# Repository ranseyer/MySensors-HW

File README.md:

View this project on [CADLAB.io](https://cadlab.io/project/1149). 

# MySensors-HW

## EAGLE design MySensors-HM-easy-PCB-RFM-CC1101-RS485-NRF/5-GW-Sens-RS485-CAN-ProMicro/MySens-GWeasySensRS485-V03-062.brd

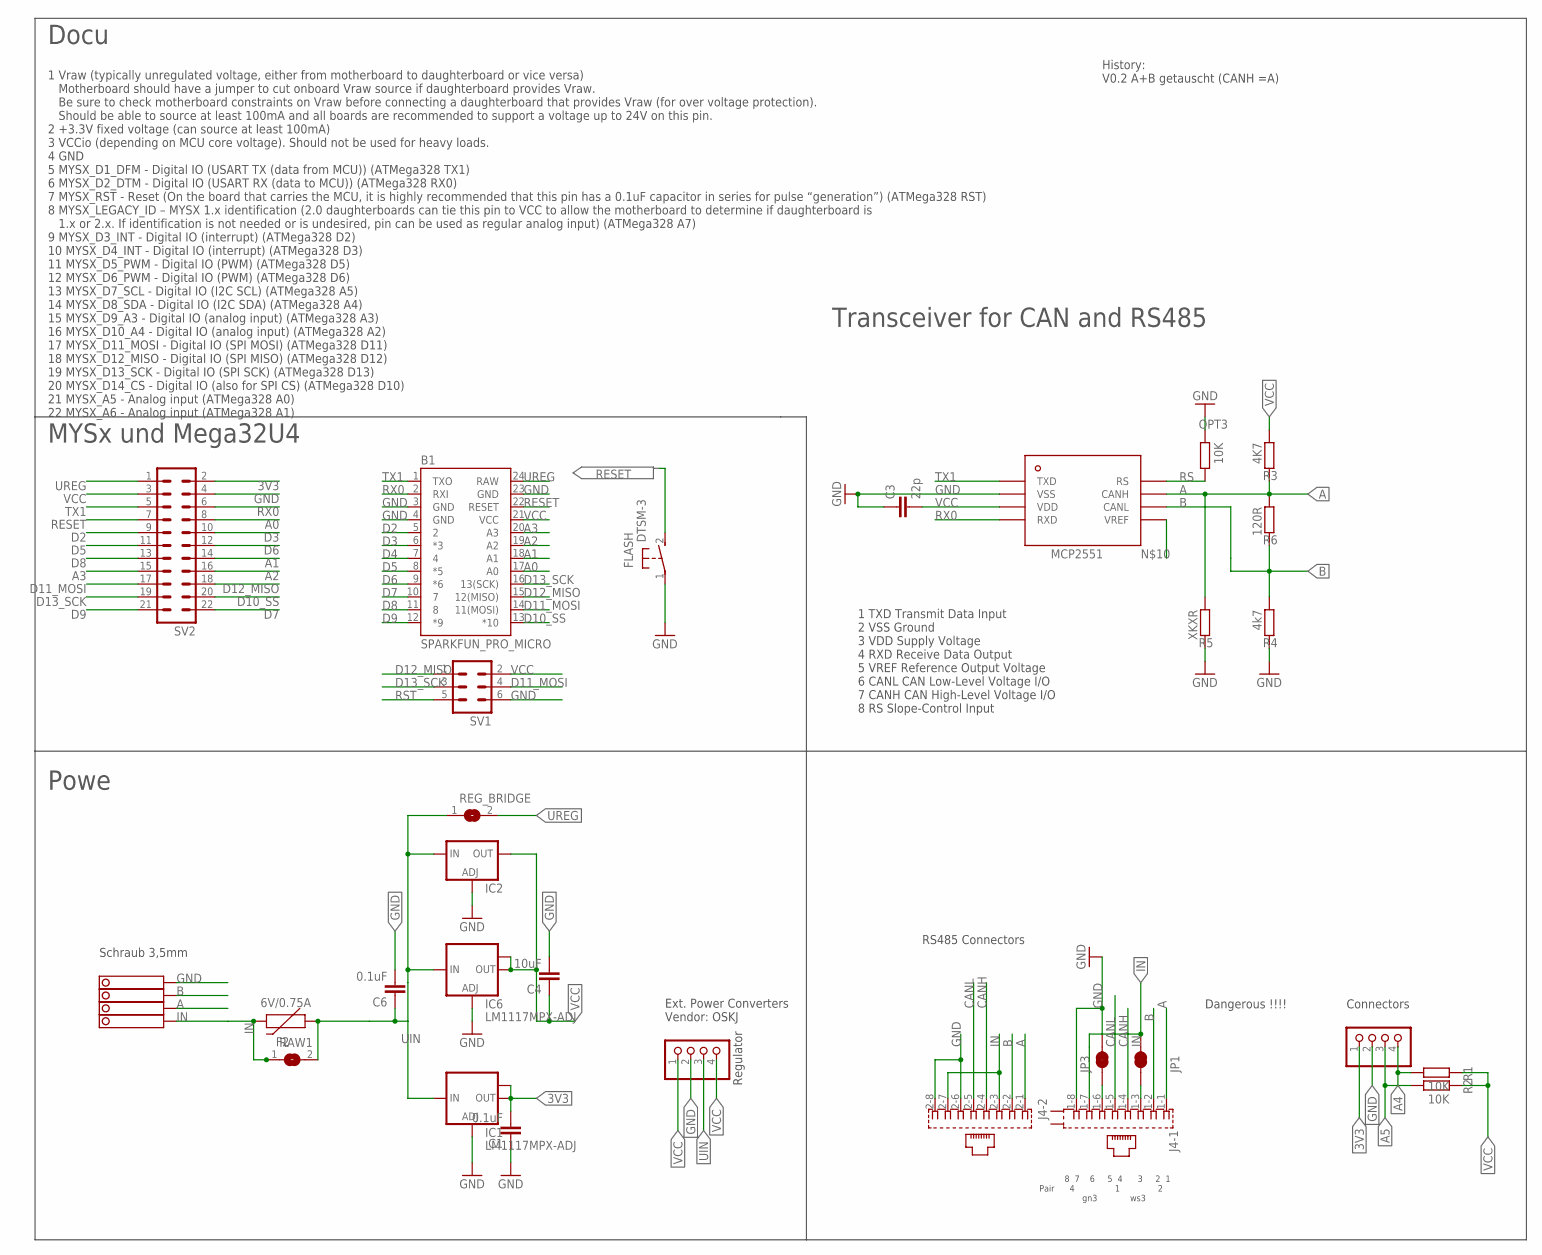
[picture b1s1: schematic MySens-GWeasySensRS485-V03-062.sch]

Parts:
B1: SPARKFUN_PRO_MICRO
C1, C6: 0.1uF; C1206
C3: 22p; C0805
C4: 10uF; C1210
F2: 6V/0.75A; 1206
FLASH: DTSM-3
I2C: PINHD-1X04_2.54-S; 1X04-S
IC1, IC6: LM1117MPX-ADJ; SOT223
IC2: LD117ADT50TR; DPACK
J4: RJ45_2X_S
JP1, JP3: JUMPER-SMT_2_NC_TRACE_SILK; SMT-JUMPER_2_NC_TRACE_SILK
OPT3: 10K; R0805
R1, R2: 10K; R0805
R3: 4K7; R0805
R4: 4k7; R0805
R5: XKXR; R0805
R6: 120R; R0805
RAW1: SJ
REG_BRIDGE: SJ
STEPDWN: PINHD-1X04_2.54-S; 1X04-S
SV1: MA03-2
SV2: MA11-2
U$1: MCP2551; SOIC-8
X4: 1751264

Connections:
1: J4.1-3 (3), JP1.1
2: J4.1-6 (6), JP3.1
3V3: C1.2, I2C.1, IC1.2 (OUT), IC1.TAB (OUT1), SV2.2
A: J4.1-1 (1), J4.2-1 (1), R3.2, R5.1, R6.1, U$1.CANH, X4.2
A0: B1.17 (A0), SV2.8
A1: B1.18 (A1), SV2.14
A2: B1.19 (A2), SV2.16
A3: B1.20 (A3), SV2.15
A4: I2C.4, R1.2
A5: I2C.3, R2.2
B: J4.1-2 (2), J4.2-2 (2), R4.1, R6.2, U$1.CANL, X4.3
CANH: J4.1-4 (4), J4.2-4 (4)
CANL: J4.1-5 (5), J4.2-5 (5)
D2: B1.5 (2), SV2.9
D3: B1.6 (*3), SV2.10
D4: B1.7 (4)
D5: B1.8 (*5), SV2.11
D6: B1.9 (*6), SV2.12
D7: B1.10 (7), SV2.22
D8: B1.11 (8), SV2.13
D9: B1.12 (*9), SV2.21
D10_SS: B1.13 (*10), SV2.20
D11_MOSI: B1.14 (11(MOSI)), SV1.4, SV2.17
D12_MISO: B1.15 (12(MISO)), SV1.1, SV2.18
D13_SCK: B1.16 (13(SCK)), SV1.3, SV2.19
GND: B1.3 (GND), B1.4 (GND), B1.23 (GND), C1.1, C3.1, C4.2, C6.2, FLASH.1, I2C.2, IC1.1 (ADJ), IC2.1 (ADJ), IC6.1 (ADJ), J4.1-8 (8), J4.2-6 (6), J4.2-8 (8), JP3.2, OPT3.1, R4.2, R5.2, STEPDWN.2, SV1.6, SV2.4, U$1.VSS, X4.4
IN: F2.2, J4.1-7 (7), J4.2-3 (3), J4.2-7 (7), JP1.2, RAW1.1, X4.1
RESET: B1.22 (RESET), FLASH.2, SV2.7
RS: OPT3.2, U$1.RS
RST: SV1.5
RX0: B1.2 (RXI), SV2.6, U$1.RXD
TX1: B1.1 (TXO), SV2.5, U$1.TXD
UIN: C6.1, F2.1, IC1.3 (IN), IC2.3 (IN), IC6.3 (IN), RAW1.2, REG_BRIDGE.1, STEPDWN.3
UREG: B1.24 (RAW), REG_BRIDGE.2, SV2.1
VCC: B1.21 (VCC), C3.2, C4.1, IC2.4 (OUT), IC6.2 (OUT), IC6.TAB (OUT1), R1.1, R2.1, R3.1, STEPDWN.1, STEPDWN.4, SV1.2, SV2.3, U$1.VDD

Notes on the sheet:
Connectors
8 7 6 5 4 3 2 1 Pair 4 1 2 gn3 ws3
Dangerous !!!!
RS485 Connectors
Schraub 3,5mm
Ext. Power Converters Vendor: OSKJ
Regulator
1 TXD Transmit Data Input 2 VSS Ground 3 VDD Supply Voltage 4 RXD Receive Data Output 5 VREF Reference Output Voltage 6 CANL CAN Low-Level Voltage I/O 7 CANH CAN High-Level Voltage I/O 8 RS Slope-Control Input
1 Vraw (typically unregulated voltage, either from motherboard to daughterboard or vice versa) Motherboard should have a jumper to cut onboard Vraw source if daughterboard provides Vraw. Be sure to check motherboard constraints on Vraw before connecting a daughterboard that provides Vraw (for over 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
Transceiver for CAN and RS485
MYSx und Mega32U4
Powe
Docu
History: V0.2 A+B getauscht (CANH =A)

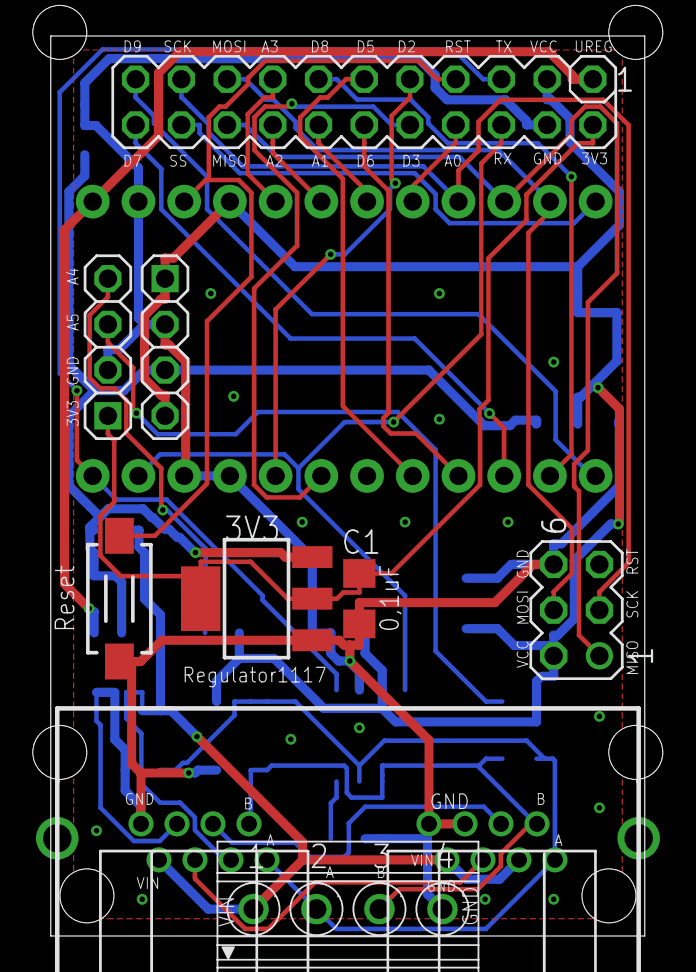
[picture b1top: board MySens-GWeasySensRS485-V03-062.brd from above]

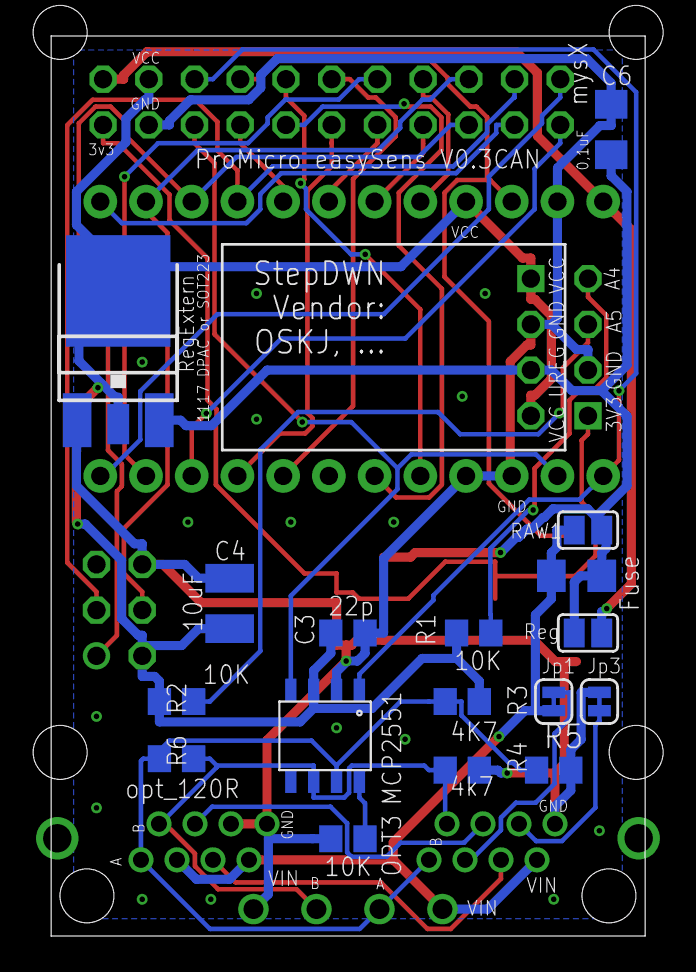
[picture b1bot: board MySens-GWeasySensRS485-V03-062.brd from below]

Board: 2 copper layers, 33.0 x 50.0 mm, 28 parts (18 on the bottom side), 33 nets.

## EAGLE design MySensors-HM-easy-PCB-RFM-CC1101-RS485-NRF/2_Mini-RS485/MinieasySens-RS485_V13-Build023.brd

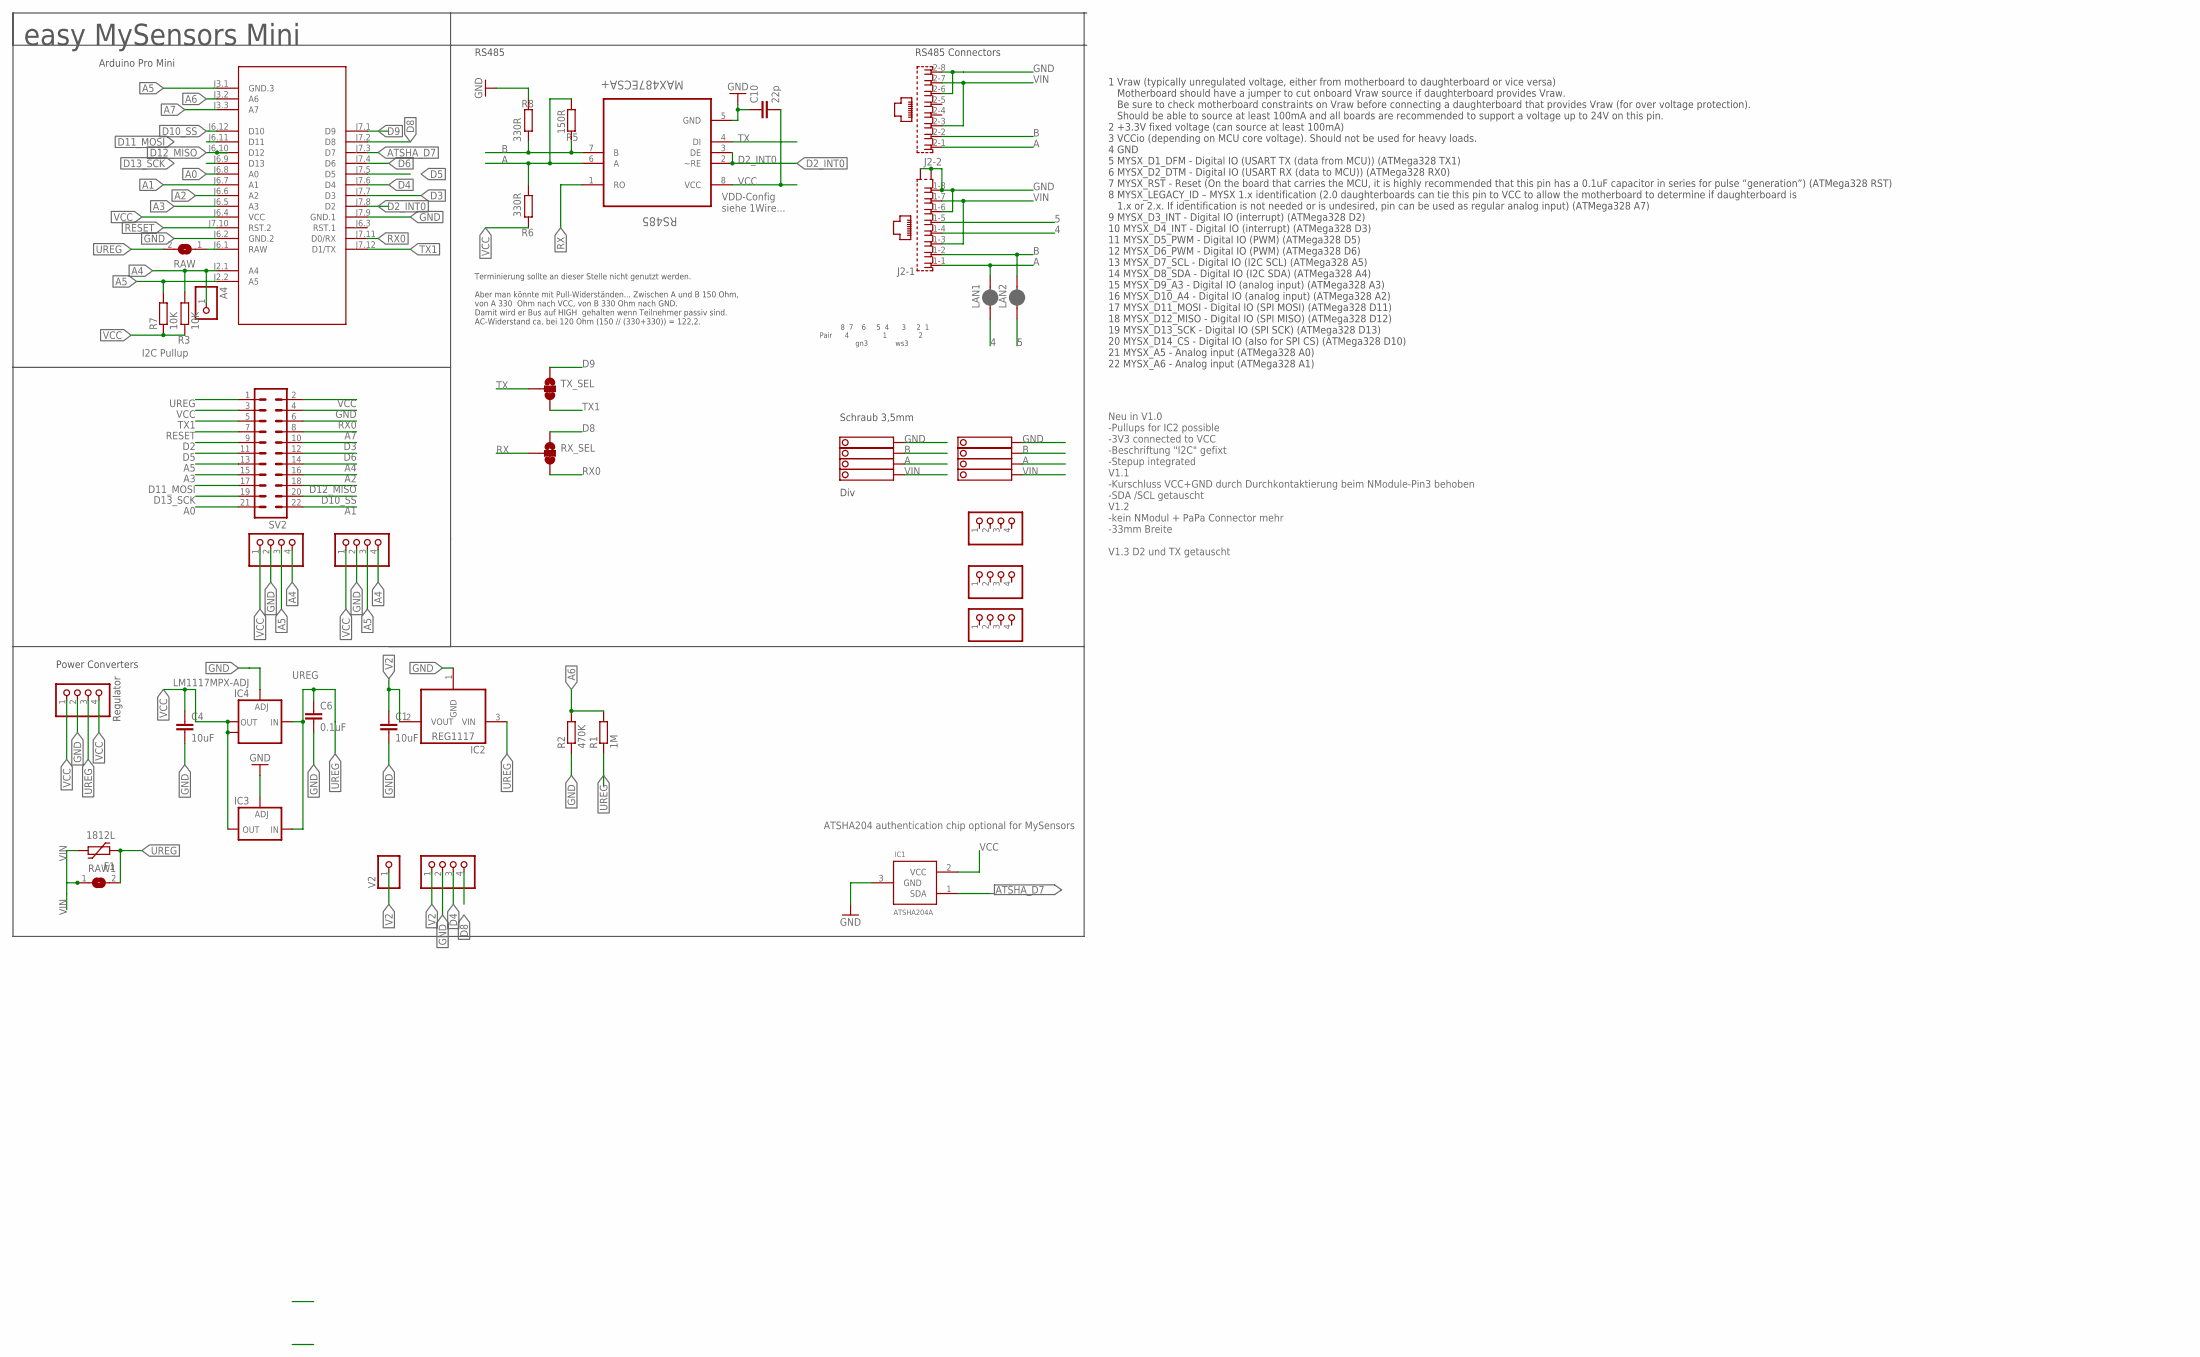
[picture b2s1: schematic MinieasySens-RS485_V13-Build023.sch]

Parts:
A4: PINHD-1X1; 1X01
BH1750: PINHD-1X04_2.54-S; 1X04-S
C1, C4: 10uF; C1210
C6: 0.1uF; C1206
C10: 22p; C0805
F1: 1812L
I2C-1: PINHD-1X04_2.54-S; 1X04-S
IC1: ATSHA204A; SOT23
IC2: REG1117; SOT223
IC3: LD117ADT50TR; DPACK
IC4: LM1117MPX-ADJ; SOT223
J2: RJ45_2X_NARROW_SHILDPINS_NOCASE
JP1, JP2, JP4: PINHD-1X04_2.54-S; 1X04-S
LAN1, LAN2: JUMPER-SMT_2_NC_PASTE_SILK; SMT-JUMPER_2_NC_PASTE_SILK
M1: ARDUINO-PRO-MINI-3.3V#NP; ARDUINO-PRO-MINI#NP
R1: 1M; R0805
R2: 470K; R0805
R3, R7: 10K; R0805
R5: 150R; R0805
R6, R8: 330R; R0805
RAW, RAW1: SJ
RS485: MAX487ECSA+; SOIC127P600X175-8N
RX_SEL: JUMPER-SMT_3_1-NC_TRACE_SILK; SMT-JUMPER_3_1-NC_TRACE_SILK
STEPDWN: PINHD-1X04_2.54-S; 1X04-S
SV2: MA11-2
TX_SEL: JUMPER-SMT_3_1-NC_TRACE_SILK; SMT-JUMPER_3_1-NC_TRACE_SILK
V2: PINHD-1X1; 1X01
V2-: PINHD-1X04_2.54-S; 1X04-S
X1, X4: 1751264

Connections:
4: J2.1-4 (4), LAN1.1
5: J2.1-5 (5), LAN2.1
A: J2.1-1 (1), J2.2-1 (1), LAN1.2, R5.1, R6.2, RS485.6 (A), X1.2, X4.2
A0: M1.J6.8 (A0), SV2.21
A1: M1.J6.7 (A1), SV2.22
A2: M1.J6.6 (A2), SV2.16
A3: M1.J6.5 (A3), SV2.15
A4: A4.1, BH1750.4, I2C-1.4, M1.J2.1 (A4), R3.2, SV2.14
A5: BH1750.3, I2C-1.3, M1.J2.2 (A5), M1.J3.1 (GND.3), R7.2, SV2.13
A6: M1.J3.2 (A6), R1.2, R2.2
A7: M1.J3.3 (A7), SV2.8
ATSHA_D7: IC1.1 (SDA), M1.J7.3 (D7)
B: J2.1-2 (2), J2.2-2 (2), LAN2.2, R5.2, R8.1, RS485.7 (B), X1.3, X4.3
D2: SV2.9
D2_INT0: M1.J7.8 (D2), RS485.2 (~RE), RS485.3 (DE)
D3: M1.J7.7 (D3), SV2.10
D4: M1.J7.6 (D4), V2-.3
D5: M1.J7.5 (D5), SV2.11
D6: M1.J7.4 (D6), SV2.12
D8: M1.J7.2 (D8), RX_SEL.1, V2-.4
D9: M1.J7.1 (D9), TX_SEL.1
D10_SS: M1.J6.12 (D10), SV2.20
D11_MOSI: M1.J6.11 (D11), SV2.17
D12_MISO: M1.J6.10 (D12), SV2.18
D13_SCK: M1.J6.9 (D13), SV2.19
GND: BH1750.2, C1.2, C4.2, C6.2, C10.1, I2C-1.2, IC1.3 (GND), IC2.1 (GND), IC3.1 (ADJ), IC4.1 (ADJ), J2.1-6 (6), J2.1-8 (8), J2.2-6 (6), J2.2-8 (8), J2.G1 (S1), J2.G3 (S2), M1.J6.2 (GND.2), M1.J7.9 (GND.1), R2.1, R8.2, RS485.5 (GND), STEPDWN.2, SV2.4, V2-.2, X1.4, X4.4
RAW: M1.J6.1 (RAW), RAW.1
RESET: M1.J7.10 (RST.2), SV2.7
RX: RS485.1 (RO), RX_SEL.2
RX0: M1.J7.11 (D0/RX), RX_SEL.3, SV2.6
TX: RS485.4 (DI), TX_SEL.2
TX1: M1.J7.12 (D1/TX), SV2.5, TX_SEL.3
UREG: C6.1, F1.P$1 (1), IC2.3 (VIN), IC3.3 (IN), IC4.3 (IN), R1.1, RAW.2, RAW1.2, STEPDWN.3, SV2.1
V2: C1.1, IC2.2 (VOUT), V2.1, V2-.1
VCC: BH1750.1, C4.1, C10.2, I2C-1.1, IC1.2 (VCC), IC3.4 (OUT), IC4.2 (OUT), IC4.TAB (OUT1), M1.J6.4 (VCC), R3.1, R6.1, R7.1, RS485.8 (VCC), STEPDWN.1, STEPDWN.4, SV2.2, SV2.3
VIN: F1.P$2 (2), J2.1-3 (3), J2.1-7 (7), J2.2-3 (3), J2.2-7 (7), RAW1.1, X1.1, X4.1

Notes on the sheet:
easy MySensors Mini
Arduino Pro Mini
ATSHA204 authentication chip optional for MySensors
Div
Neu in V1.0 -Pullups for IC2 possible -3V3 connected to VCC -Beschriftung "I2C" gefixt -Stepup integrated V1.1 -Kurschluss VCC+GND durch Durchkontaktierung beim NModule-Pin3 behoben -SDA /SCL getauscht V1.2 -kein NModul + PaPa Connector mehr -33mm Breite V1.3 D2 und TX getauscht
I2C Pullup
Power Converters
RS485
VDD-Config siehe 1Wire...
Terminierung sollte an dieser Stelle nicht genutzt werden. Aber man könnte mit Pull-Widerständen... Zwischen A und B 150 Ohm, von A 330 Ohm nach VCC, von B 330 Ohm nach GND. Damit wird er Bus auf HIGH gehalten wenn Teilnehmer passiv sind. AC-Widerstand ca. bei 120 Ohm (150 // (330+330)) = 122,2.
Schraub 3,5mm
8 7 6 5 4 3 2 1 Pair 4 1 2 gn3 ws3
Regulator
RS485 Connectors
1 Vraw (typically unregulated voltage, either from motherboard to daughterboard or vice versa) Motherboard should have a jumper to cut onboard Vraw source if daughterboard provides Vraw. Be sure to check motherboard constraints on Vraw before connecting a daughterboard that provides Vraw (for over 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

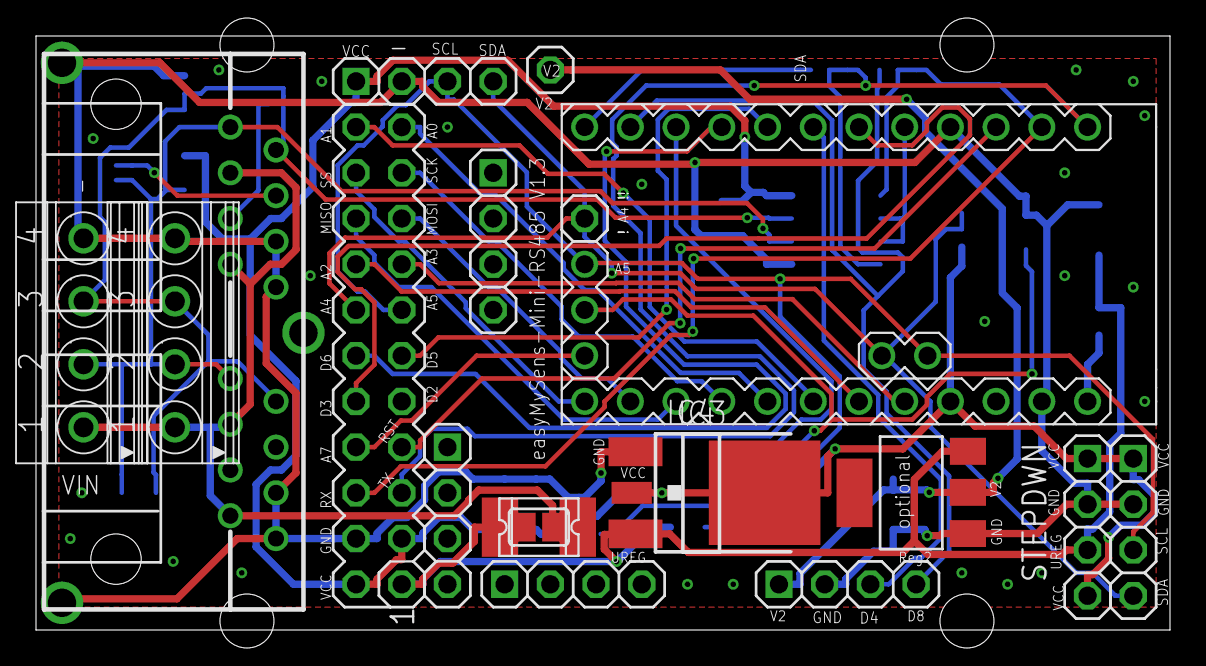
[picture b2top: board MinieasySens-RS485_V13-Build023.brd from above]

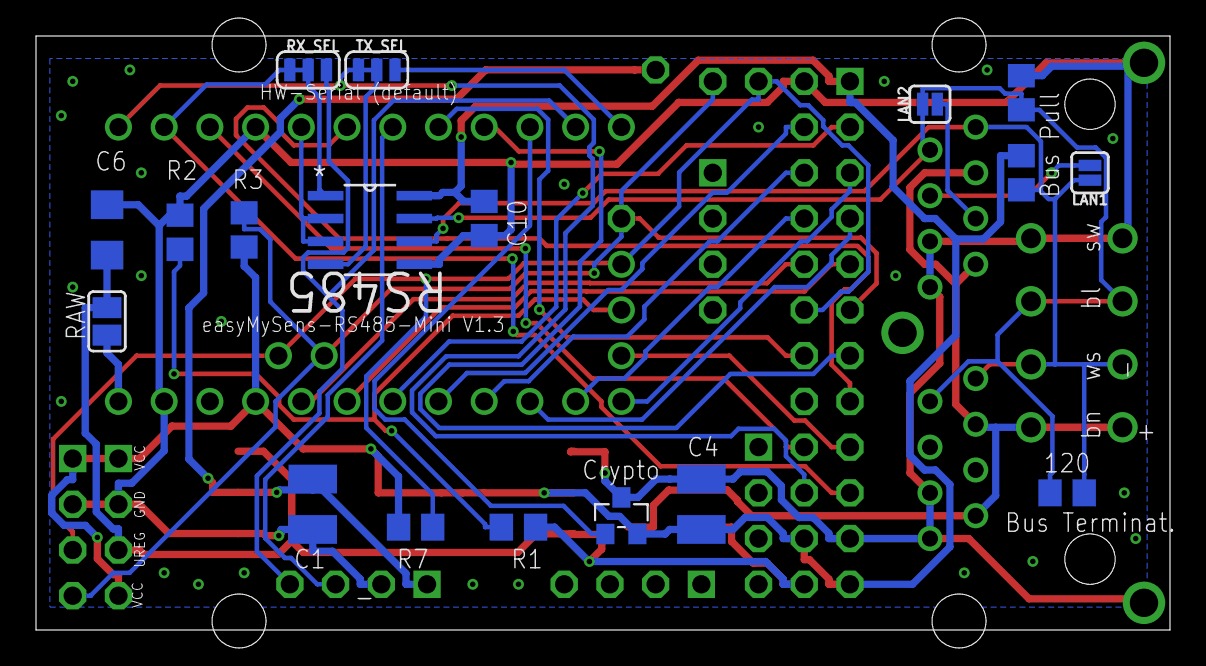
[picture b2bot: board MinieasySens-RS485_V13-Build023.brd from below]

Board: 2 copper layers, 63.0 x 33.0 mm, 37 parts (18 on the bottom side), 35 nets.

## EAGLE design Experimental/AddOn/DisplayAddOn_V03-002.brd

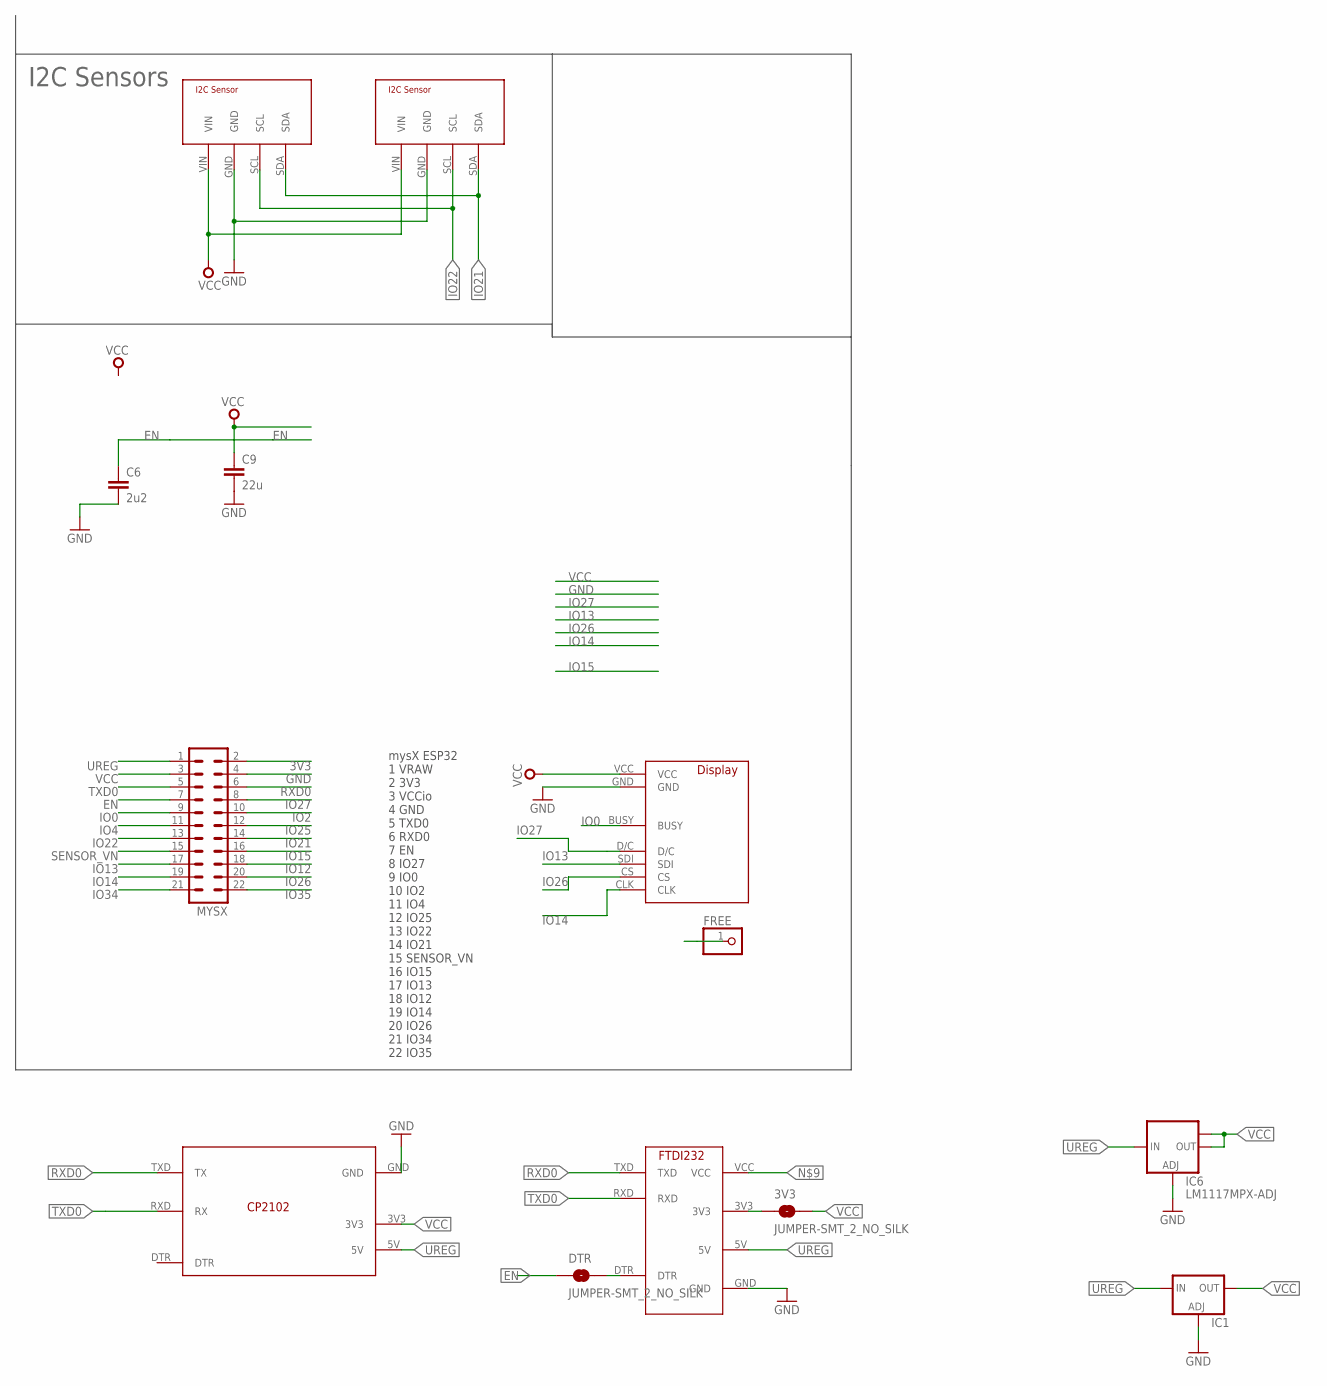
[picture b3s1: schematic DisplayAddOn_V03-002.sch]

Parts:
3V3: JUMPER-SMT_2_NO_SILK; SMT-JUMPER_2_NO_SILK
C6: 2u2; C0805
C9: 22u; C0805
DTR: JUMPER-SMT_2_NO_SILK; SMT-JUMPER_2_NO_SILK
FREE: PINHD-1X1; 1X01
HELTEK: ZUCZUG_1.54; ZUCZUG_1.54INCH
IC1: LD117ADT50TR; DPACK
IC6: LM1117MPX-ADJ; SOT223
MYSX: MA11-2
U$1: CP2101; CP2101-BEAKOUT
U$2, U$4: I2C-BREAKOUT; I2C_BREAKOUT
U$3: FTDI232; FTDI232-LARGE-LESS-PINS

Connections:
3V3: MYSX.2
EN: C6.1, DTR.1, MYSX.7
FREE: FREE.1
GND: C6.2, C9.2, HELTEK.GND, IC1.1 (ADJ), IC6.1 (ADJ), MYSX.4, U$1.GND, U$2.GND, U$3.GND, U$4.GND
IO0: HELTEK.BUSY, MYSX.9
IO2: MYSX.10
IO4: MYSX.11
IO12: MYSX.18
IO13: HELTEK.SDI, MYSX.17
IO14: HELTEK.CLK, MYSX.19
IO15: MYSX.16
IO21: MYSX.14, U$2.SDA, U$4.SDA
IO22: MYSX.13, U$2.SCL, U$4.SCL
IO25: MYSX.12
IO26: HELTEK.CS, MYSX.20
IO27: HELTEK.D/C, MYSX.8
IO34: MYSX.21
IO35: MYSX.22
unnamed: DTR.2, U$3.DTR
unnamed: 3V3.1, U$3.3V3
RXD0: MYSX.6, U$1.TXD (TX), U$3.TXD
SENSOR_VN: MYSX.15
TXD0: MYSX.5, U$1.RXD (RX), U$3.RXD
UREG: IC1.3 (IN), IC6.3 (IN), MYSX.1, U$1.5V, U$3.5V
VCC: 3V3.2, C9.1, HELTEK.VCC, IC1.4 (OUT), IC6.2 (OUT), IC6.TAB (OUT1), MYSX.3, U$1.3V3, U$2.VIN, U$4.VIN

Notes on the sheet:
mysX ESP32 1 VRAW 2 3V3 3 VCCio 4 GND 5 TXD0 6 RXD0 7 EN 8 IO27 9 IO0 10 IO2 11 IO4 12 IO25 13 IO22 14 IO21 15 SENSOR_VN 16 IO15 17 IO13 18 IO12 19 IO14 20 IO26 21 IO34 22 IO35
I2C Sensors

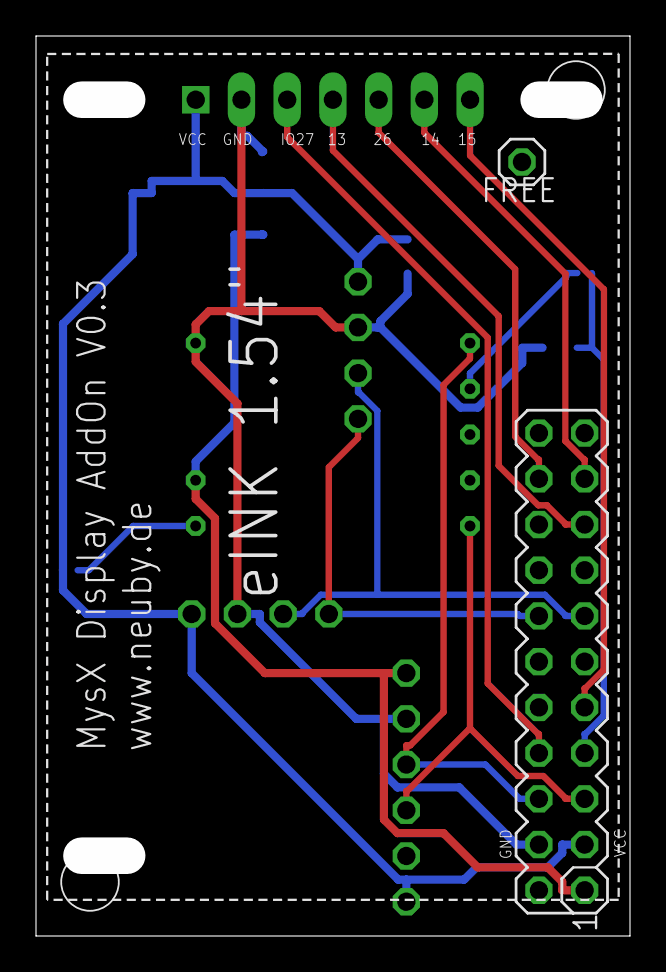
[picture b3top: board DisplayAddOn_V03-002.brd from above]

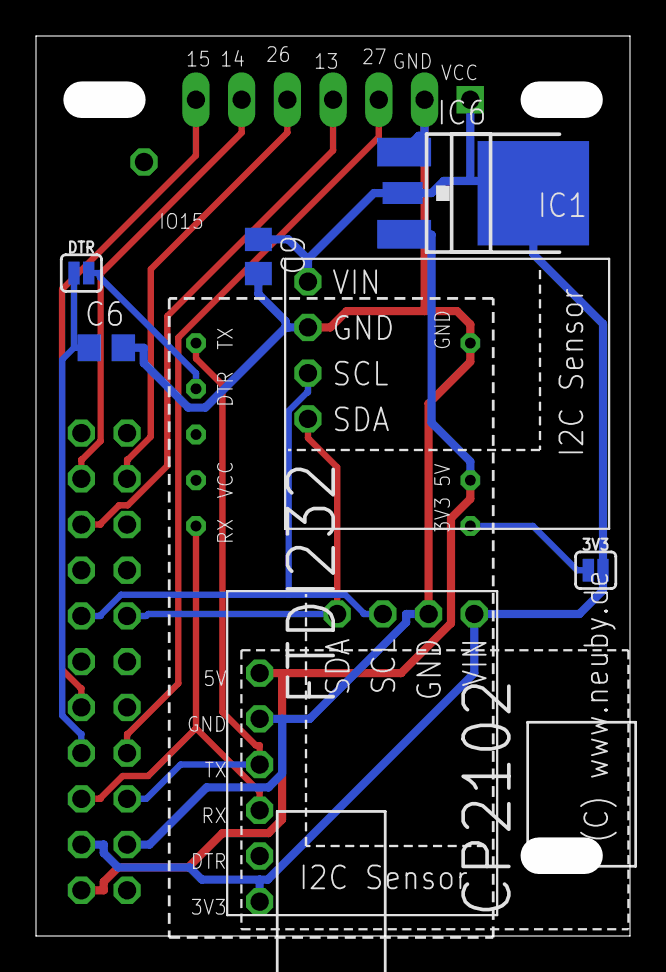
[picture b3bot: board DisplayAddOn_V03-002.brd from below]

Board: 2 copper layers, 31.0 x 48.0 mm, 13 parts (10 on the bottom side), 15 nets.

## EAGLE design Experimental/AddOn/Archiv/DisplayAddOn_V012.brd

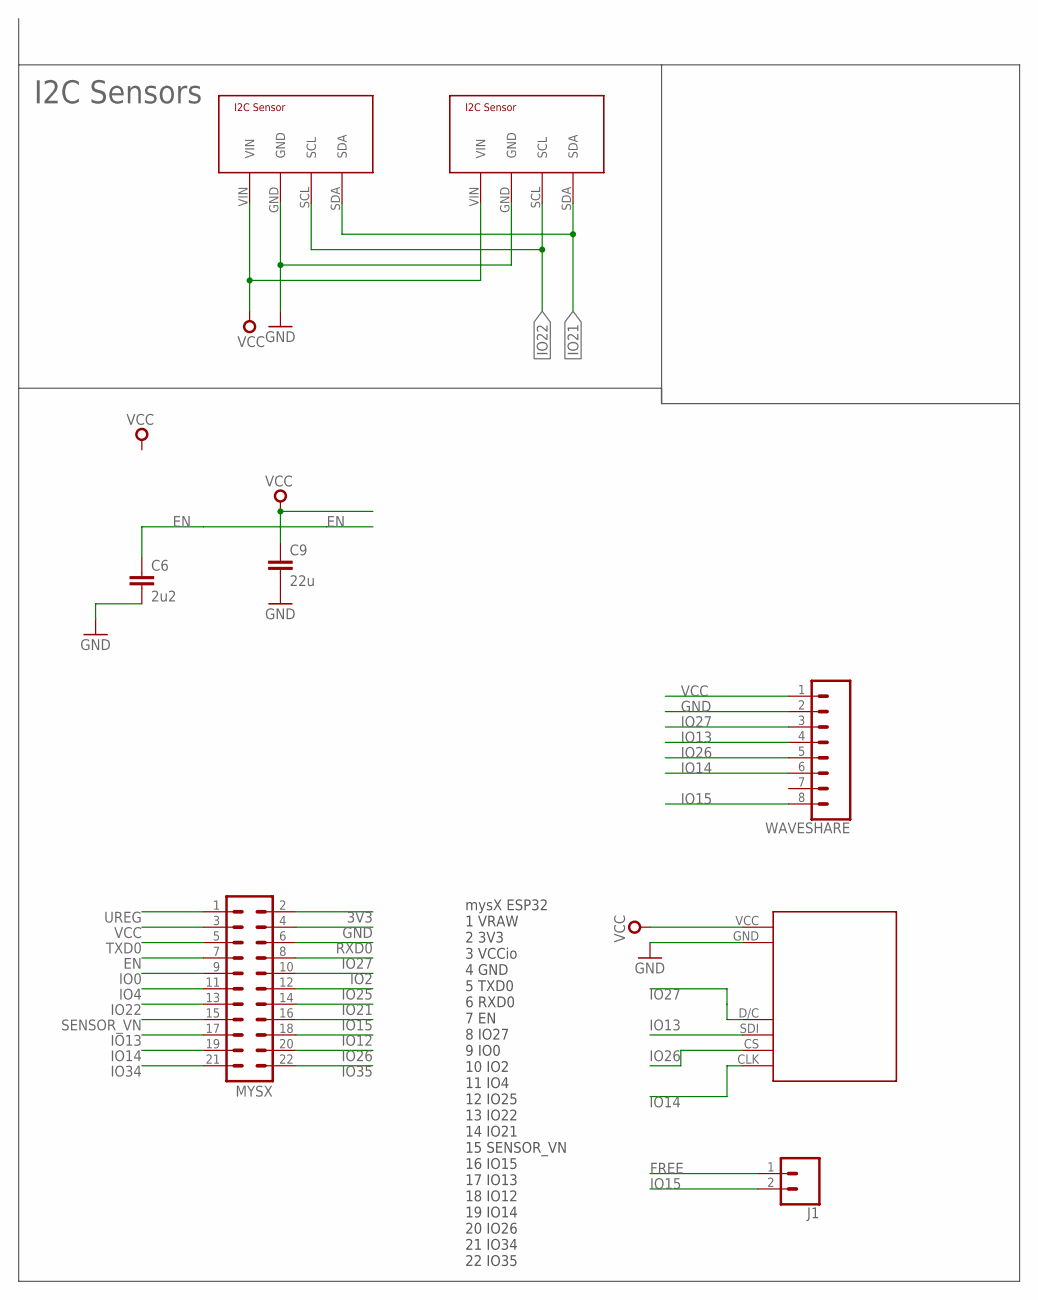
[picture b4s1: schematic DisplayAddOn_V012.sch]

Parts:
C6: 2u2; C0805
C9: 22u; C0805
HELTEK: HELTEC_1.54STANDARD1; HELTEC_1.54INCH
J1: CONN_02; 1X02
MYSX: MA11-2
U$2, U$4: I2C-BREAKOUT; I2C_BREAKOUT
WAVESHARE: CONN_08"; 1X08

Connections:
3V3: MYSX.2
EN: C6.1, MYSX.7
FREE: J1.1
GND: C6.2, C9.2, HELTEK.GND, MYSX.4, U$2.GND, U$4.GND, WAVESHARE.2
IO0: MYSX.9
IO2: MYSX.10
IO4: MYSX.11
IO12: MYSX.18
IO13: HELTEK.SDI, MYSX.17, WAVESHARE.4
IO14: HELTEK.CLK, MYSX.19, WAVESHARE.6
IO15: J1.2, MYSX.16, WAVESHARE.8
IO21: MYSX.14, U$2.SDA, U$4.SDA
IO22: MYSX.13, U$2.SCL, U$4.SCL
IO25: MYSX.12
IO26: HELTEK.CS, MYSX.20, WAVESHARE.5
IO27: HELTEK.D/C, MYSX.8, WAVESHARE.3
IO34: MYSX.21
IO35: MYSX.22
RXD0: MYSX.6
SENSOR_VN: MYSX.15
TXD0: MYSX.5
UREG: MYSX.1
VCC: C9.1, HELTEK.VCC, MYSX.3, U$2.VIN, U$4.VIN, WAVESHARE.1

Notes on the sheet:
mysX ESP32 1 VRAW 2 3V3 3 VCCio 4 GND 5 TXD0 6 RXD0 7 EN 8 IO27 9 IO0 10 IO2 11 IO4 12 IO25 13 IO22 14 IO21 15 SENSOR_VN 16 IO15 17 IO13 18 IO12 19 IO14 20 IO26 21 IO34 22 IO35
I2C Sensors

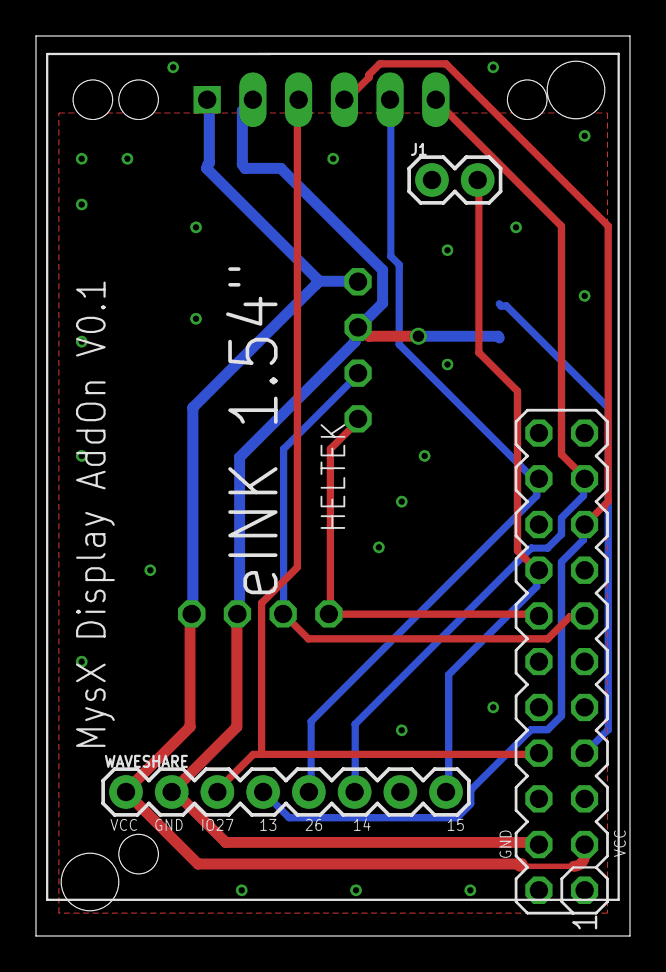
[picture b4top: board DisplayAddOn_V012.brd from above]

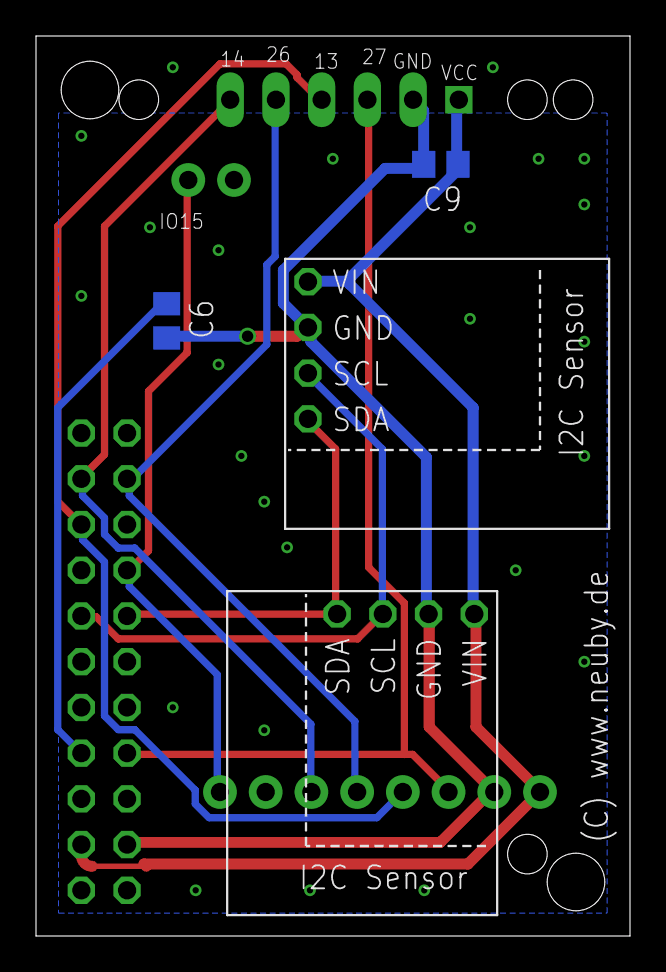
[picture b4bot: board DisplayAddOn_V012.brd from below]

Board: 2 copper layers, 33.0 x 50.0 mm, 8 parts (4 on the bottom side), 10 nets.

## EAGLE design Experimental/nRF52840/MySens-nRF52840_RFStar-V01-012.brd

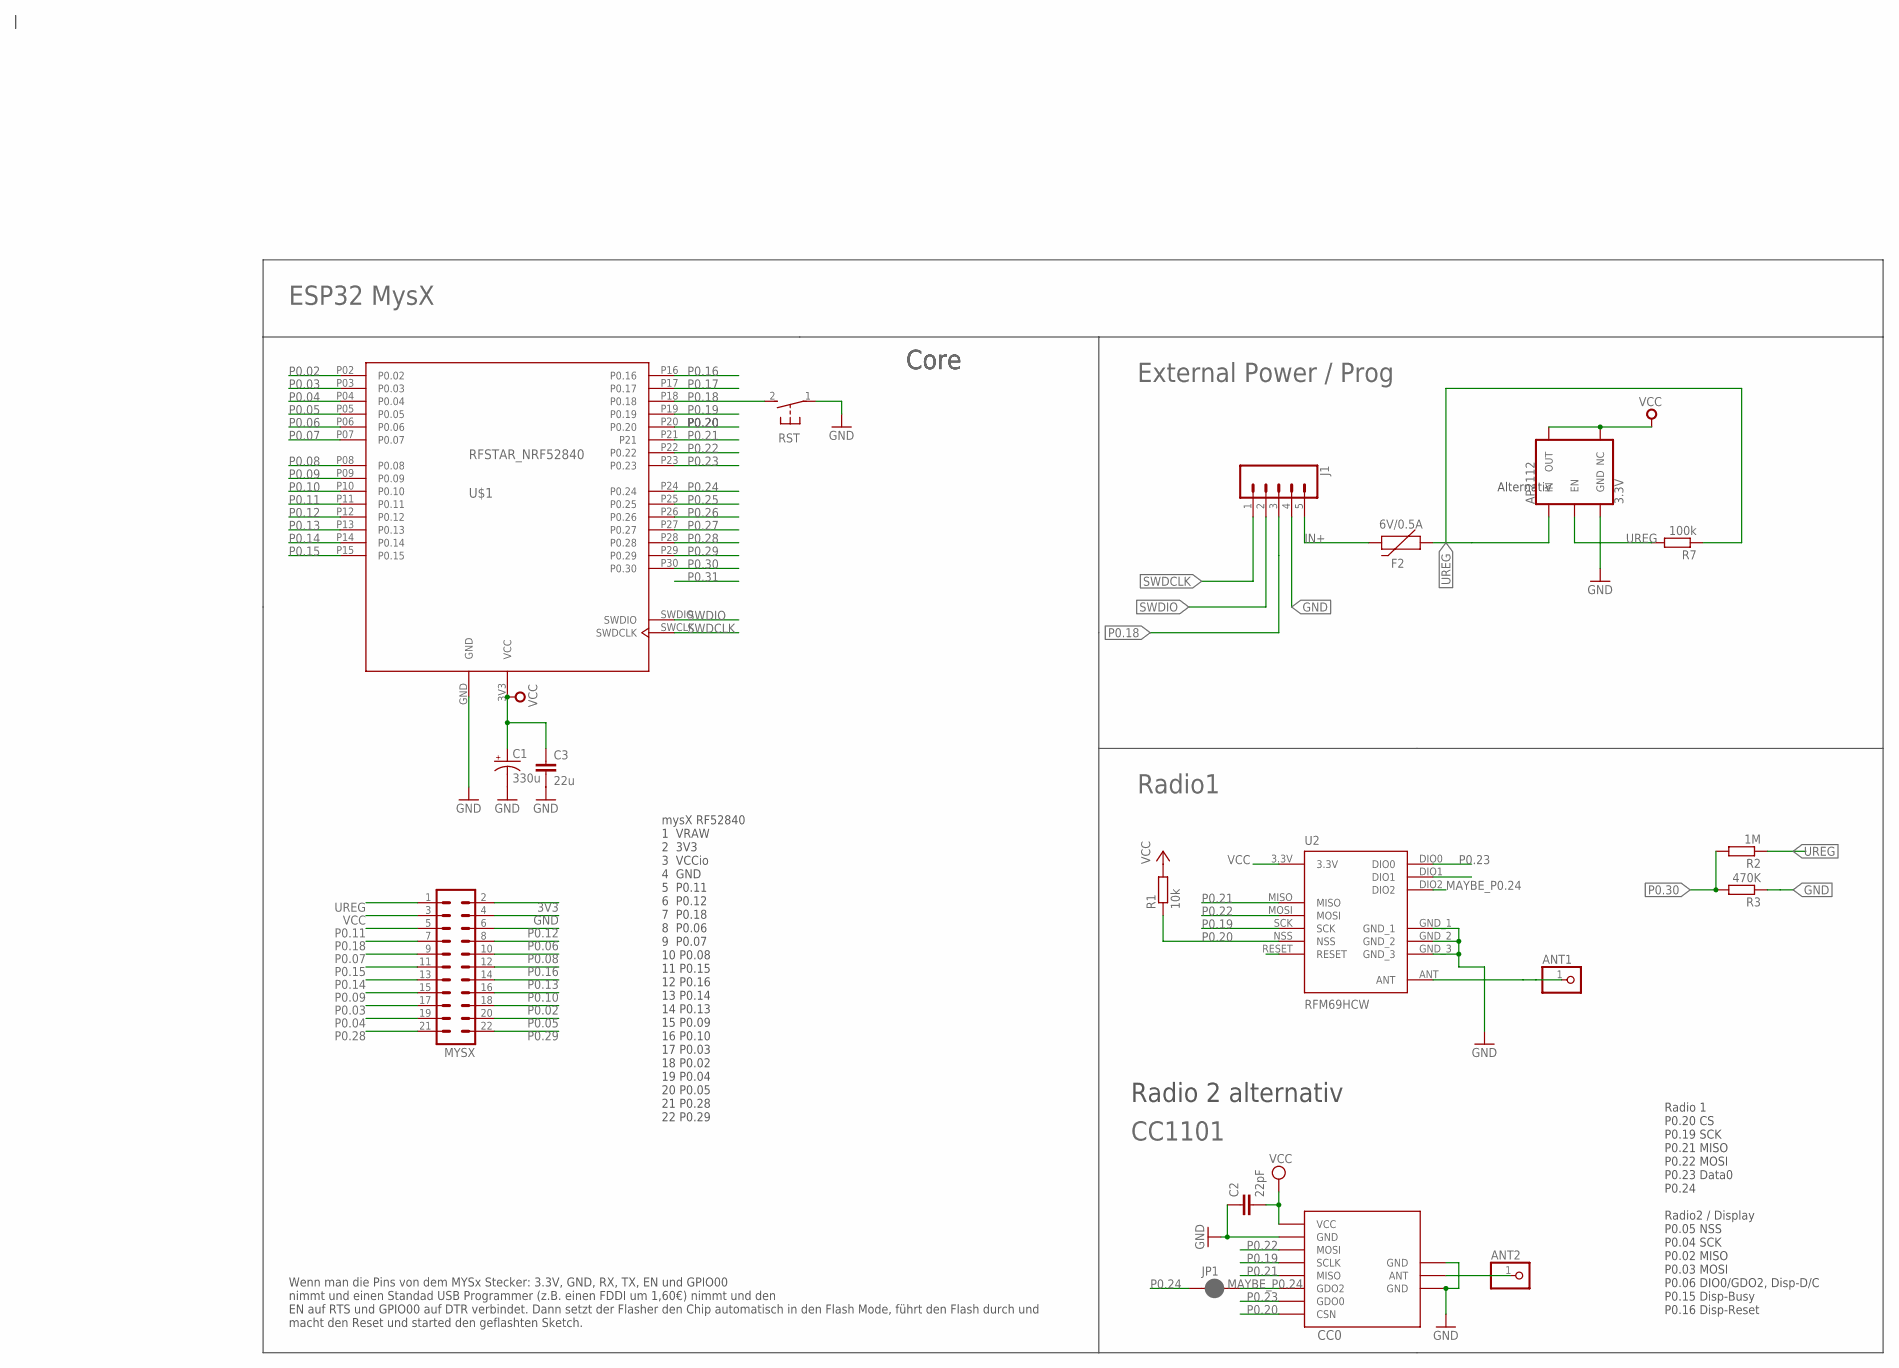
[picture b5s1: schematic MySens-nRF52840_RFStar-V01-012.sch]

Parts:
ANT1, ANT2: PINHD-1X1; 1X01
AP2112: 3.3V; SOT23-5
C1: 330u; VISHAY_C
C2: 22pF; C0805
C3: 22u; C0805
CC0: CC1101; CC1101_MODULE1_SMD
F2: 6V/0.5A; 1206
J1: CONN_05LOCK; 1X05_LOCK
JP1: JUMPER-SMT_2_NC_PASTE_NO-SILK; SMT-JUMPER_2_NC_PASTE_NO-SILK
MYSX: MA11-2
R1: 10k; M0805
R2: 1M; M0805
R3: 470K; M0805
R7: 100k; M0805
RST: DTSM-3
U2: RFM69HCW; RFM69HCW-XXXS2
U$1: RFSTAR_NRF52840

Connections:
3V3: MYSX.2
ANT0: ANT2.1, CC0.ANT
ANT1: ANT1.1, U2.ANT
GND: AP2112.2 (GND), C1.-, C2.1, C3.2, CC0.GND@0 (GND), CC0.GND@1 (GND), CC0.GND@2 (GND), J1.4, MYSX.4, R3.1, RST.1, U2.GND_1, U2.GND_2, U2.GND_3, U$1.GND
IN+: F2.2, J1.5
MAYBE_P0.24: CC0.GDO2, JP1.2, U2.DIO2
unnamed: AP2112.3 (EN), R7.2
P0.02: MYSX.18, U$1.P02 (P0.02)
P0.03: MYSX.17, U$1.P03 (P0.03)
P0.04: MYSX.19, U$1.P04 (P0.04)
P0.05: MYSX.20, U$1.P05 (P0.05)
P0.06: MYSX.8, U$1.P06 (P0.06)
P0.07: MYSX.9, U$1.P07 (P0.07)
P0.08: MYSX.10, U$1.P08 (P0.08)
P0.09: MYSX.15, U$1.P09 (P0.09)
P0.10: MYSX.16, U$1.P10 (P0.10)
P0.11: MYSX.5, U$1.P11 (P0.11)
P0.12: MYSX.6, U$1.P12 (P0.12)
P0.13: MYSX.14, U$1.P13 (P0.13)
P0.14: MYSX.13, U$1.P14 (P0.14)
P0.15: MYSX.11, U$1.P15 (P0.15)
P0.16: MYSX.12, U$1.P16 (P0.16)
P0.17: U$1.P17 (P0.17)
P0.18: J1.3, MYSX.7, RST.2, U$1.P18 (P0.18)
P0.19: CC0.SCLK, U2.SCK, U$1.P19 (P0.19)
P0.20: CC0.CSN, R1.1, U2.NSS, U$1.P20 (P0.20)
P0.21: CC0.MISO, U2.MISO, U$1.P21
P0.22: CC0.MOSI, U2.MOSI, U$1.P22 (P0.22)
P0.23: CC0.GDO0, U2.DIO0, U$1.P23 (P0.23)
P0.24: JP1.1, U$1.P24 (P0.24)
P0.25: U$1.P25 (P0.25)
P0.26: U$1.P26 (P0.26)
P0.27: U$1.P27 (P0.27)
P0.28: MYSX.21, U$1.P28 (P0.28)
P0.29: MYSX.22, U$1.P29 (P0.29)
P0.30: R2.2, R3.2, U$1.P30 (P0.30)
SWDCLK: J1.1, U$1.SWCLK (SWDCLK)
SWDIO: J1.2, U$1.SWDIO
UREG: AP2112.1 (IN), F2.1, MYSX.1, R2.1, R7.1
VCC: AP2112.4 (NC), AP2112.5 (OUT), C1.+, C2.2, C3.1, CC0.VCC, MYSX.3, R1.2, U2.3.3V, U$1.3V3 (VCC)

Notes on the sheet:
mysX RF52840 1 VRAW 2 3V3 3 VCCio 4 GND 5 P0.11 6 P0.12 7 P0.18 8 P0.06 9 P0.07 10 P0.08 11 P0.15 12 P0.16 13 P0.14 14 P0.13 15 P0.09 16 P0.10 17 P0.03 18 P0.02 19 P0.04 20 P0.05 21 P0.28 22 P0.29
Radio1
ESP32 MysX
Radio 2 alternativ
CC1101
Wenn man die Pins von dem MYSx Stecker: 3.3V, GND, RX, TX, EN und GPIO00 nimmt und einen Standad USB Programmer (z.B. einen FDDI um 1,60€) nimmt und den EN auf RTS und GPIO00 auf DTR verbindet. Dann setzt der Flasher den Chip automatisch in den Flash Mode, führt den Flash durch und macht den Reset 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
Alternativ
Core
External Power / Prog
Radio 1 P0.20 CS P0.19 SCK P0.21 MISO P0.22 MOSI P0.23 Data0 P0.24 Radio2 / Display P0.05 NSS P0.04 SCK P0.02 MISO P0.03 MOSI P0.06 DIO0/GDO2, Disp-D/C P0.15 Disp-Busy P0.16 Disp-Reset

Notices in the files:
parts and their libraries:
SparkFun-Connectors: Licensing: Creative Commons ShareAlike 4.0 International - https://creativecommons.org/licenses/by-sa/4.0
diy-modules: Released under the Creative Commons Attribution 4.0 International License: http://creativecommons.org/licenses/by/4.0
